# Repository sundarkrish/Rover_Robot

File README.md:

# Rover-Robot
 repository for software, hardware and reference documents related to rover robot project

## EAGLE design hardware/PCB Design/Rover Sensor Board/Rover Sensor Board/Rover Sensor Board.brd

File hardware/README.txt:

schematics, layout, 3D models, gerber files etc.

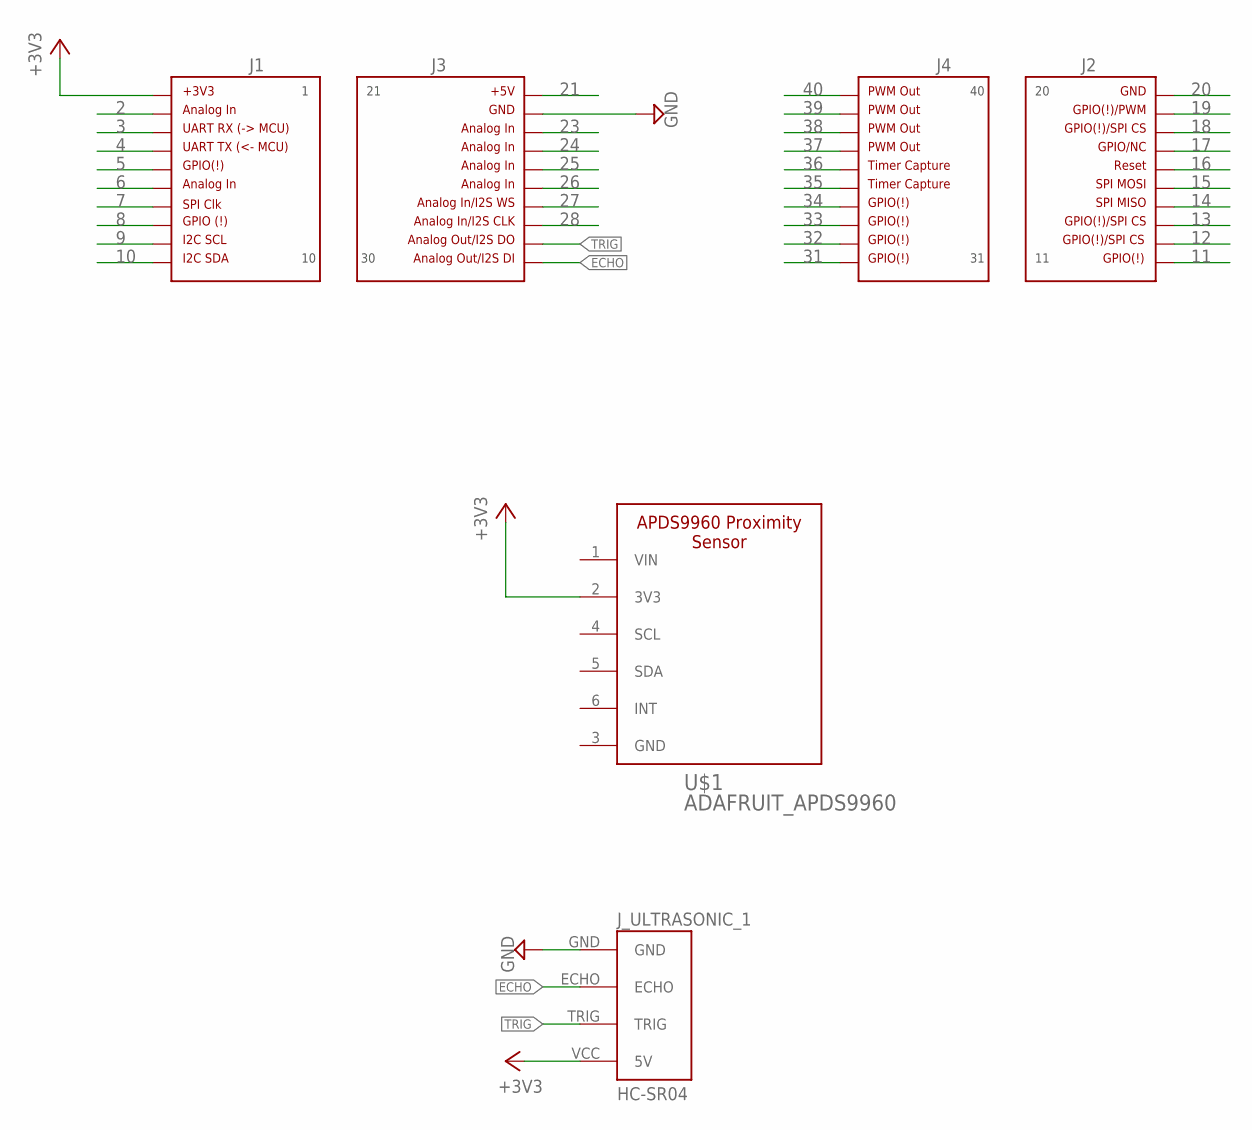
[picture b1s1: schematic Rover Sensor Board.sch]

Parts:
J1: HEADER1X10-J1SILK_LABELS; J1
J2: HEADER1X10-J2SILK_LABELS; J2
J3: HEADER1X10-J3NOSILK; 1X10-J3
J4: HEADER1X10-J4SILK_LABELS; J4
J_ULTRASONIC_1: HC-SR04; HC-SR04_FOOTPRINT
U$1: ADAFRUIT_APDS9960

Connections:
2: J1.2
3: J1.3
4: J1.4
5: J1.5
6: J1.6
7: J1.7
8: J1.8
9: J1.9
10: J1.10
11: J2.11
12: J2.12
13: J2.13
14: J2.14
15: J2.15
16: J2.16
17: J2.17
18: J2.18
19: J2.19
20: J2.20
21: J3.21
23: J3.23
24: J3.24
25: J3.25
26: J3.26
27: J3.27
28: J3.28
31: J4.31
32: J4.32
33: J4.33
34: J4.34
35: J4.35
36: J4.36
37: J4.37
38: J4.38
39: J4.39
40: J4.40
+3V3: J1.1, J_ULTRASONIC_1.VCC (5V), U$1.2 (3V3)
ECHO: J3.30, J_ULTRASONIC_1.ECHO
GND: J3.22, J_ULTRASONIC_1.GND
TRIG: J3.29, J_ULTRASONIC_1.TRIG

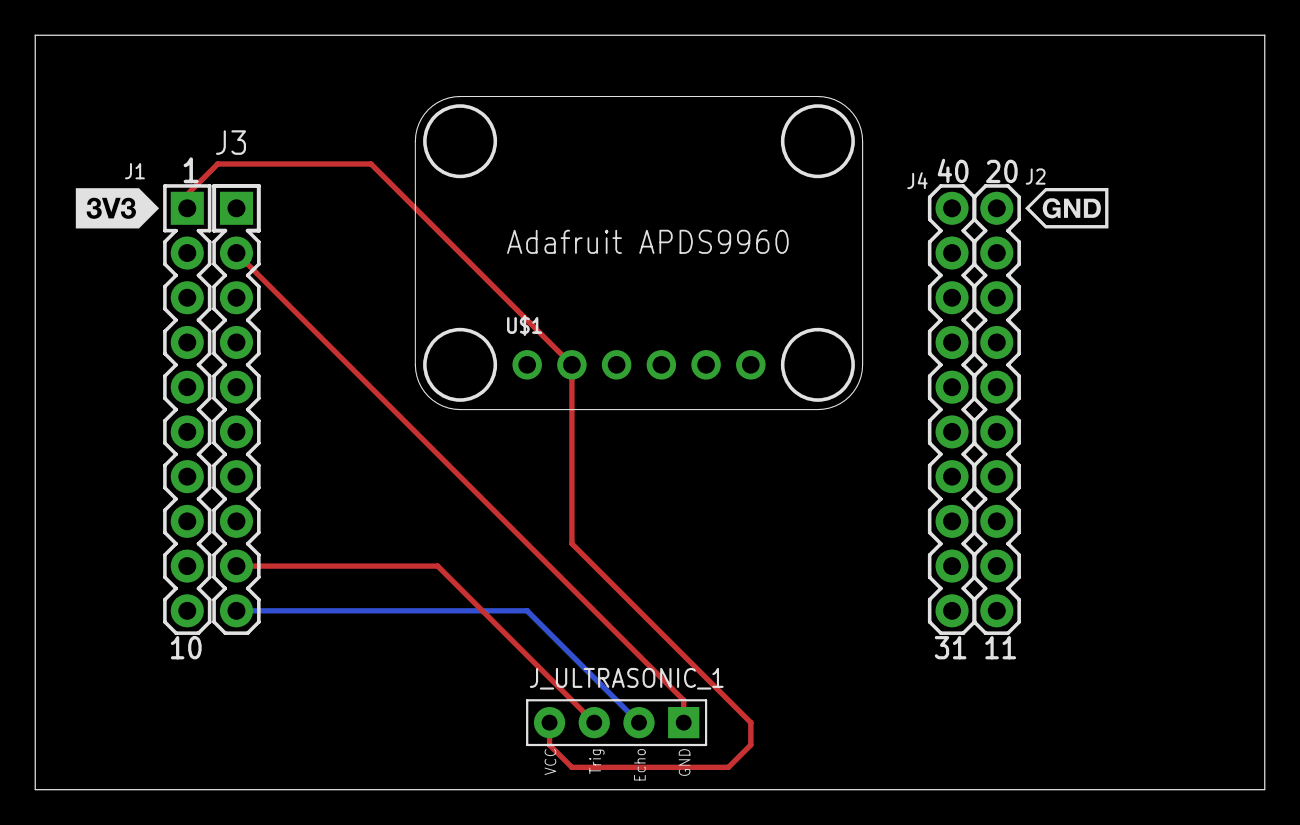
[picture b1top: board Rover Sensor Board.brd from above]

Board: 2 copper layers, 69.8 x 42.9 mm, 6 parts (0 on the bottom side), 4 nets.

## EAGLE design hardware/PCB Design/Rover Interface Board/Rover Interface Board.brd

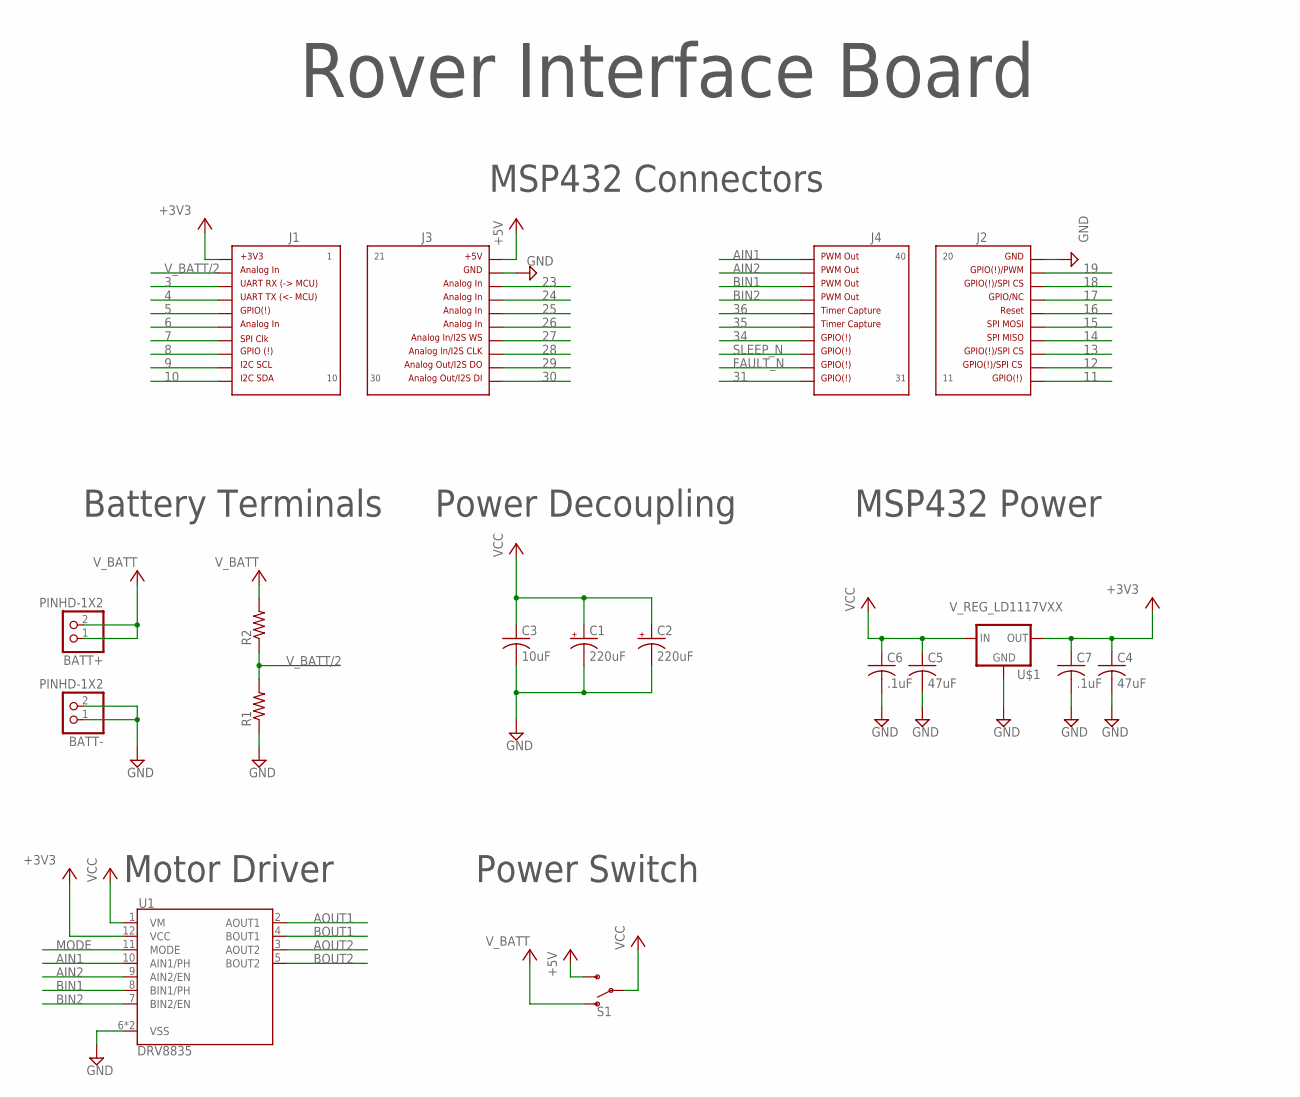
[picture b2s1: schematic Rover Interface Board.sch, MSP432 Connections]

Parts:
BATT+: PINHD-1X2; 1X02
BATT-: PINHD-1X2; 1X02
C1, C2: 220uF; CPOL-RADIAL-5MM-10MM
C3: 10uF; C025-050X050
C4, C5: 47uF; C025-050X050
C6, C7: .1uF; C025-050X050
J1: HEADER1X10-J1SILK_LABELS; J1
J2: HEADER1X10-J2SILK_LABELS; J2
J3: HEADER1X10-J3; J3
J4: HEADER1X10-J4SILK_LABELS; J4
R1, R2: R-US_0204/7; 0204/7
S1: SWITCH-SPDT-PTH-11.6X4.0MM; SWITCH_SPDT_PTH_11.6X4.0MM
U1: DRV8835; WSON-12
U$1: V_REG_LD1117VXX; 78XXL

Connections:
3: J1.3
4: J1.4
5: J1.5
6: J1.6
7: J1.7
8: J1.8
9: J1.9
10: J1.10
11: J2.11
12: J2.12
13: J2.13
14: J2.14
15: J2.15
16: J2.16
17: J2.17
18: J2.18
19: J2.19
23: J3.23
24: J3.24
25: J3.25
26: J3.26
27: J3.27
28: J3.28
29: J3.29
30: J3.30
31: J4.31
34: J4.34
35: J4.35
36: J4.36
+3V3: C4.1, C7.1, J1.1, U1.12 (VCC), U$1.GND (OUT)
+5V: J3.21, S1.3 (S)
AIN1: J4.40, U1.10 (AIN1/PH)
AIN2: J4.39, U1.9 (AIN2/EN)
AOUT1: U1.2 (AOUT1)
AOUT2: U1.3 (AOUT2)
BIN1: J4.38, U1.8 (BIN1/PH)
BIN2: J4.37, U1.7 (BIN2/EN)
BOUT1: U1.4 (BOUT1)
BOUT2: U1.5 (BOUT2)
FAULT_N: J4.32
GND: BATT-.1, BATT-.2, C1.-, C2.-, C3.2, C4.2, C5.2, C6.2, C7.2, J2.20, J3.22, R1.1, U1.6 (VSS), U1.PAD (VSS), U$1.IN (GND)
MODE: U1.11 (MODE)
SLEEP_N: J4.33
VCC: C1.+, C2.+, C3.1, C5.1, C6.1, S1.2, U1.1 (VM), U$1.OUT (IN)
V_BATT: BATT+.1, BATT+.2, R2.2, S1.1 (O)
V_BATT/2: J1.2, R1.2, R2.1

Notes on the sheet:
Rover Interface Board
Battery Terminals
Power Decoupling
MSP432 Power
MSP432 Connectors
Power Switch
Motor Driver

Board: 2 copper layers, 18 parts (0 on the bottom side), 10 nets, no tracks yet.

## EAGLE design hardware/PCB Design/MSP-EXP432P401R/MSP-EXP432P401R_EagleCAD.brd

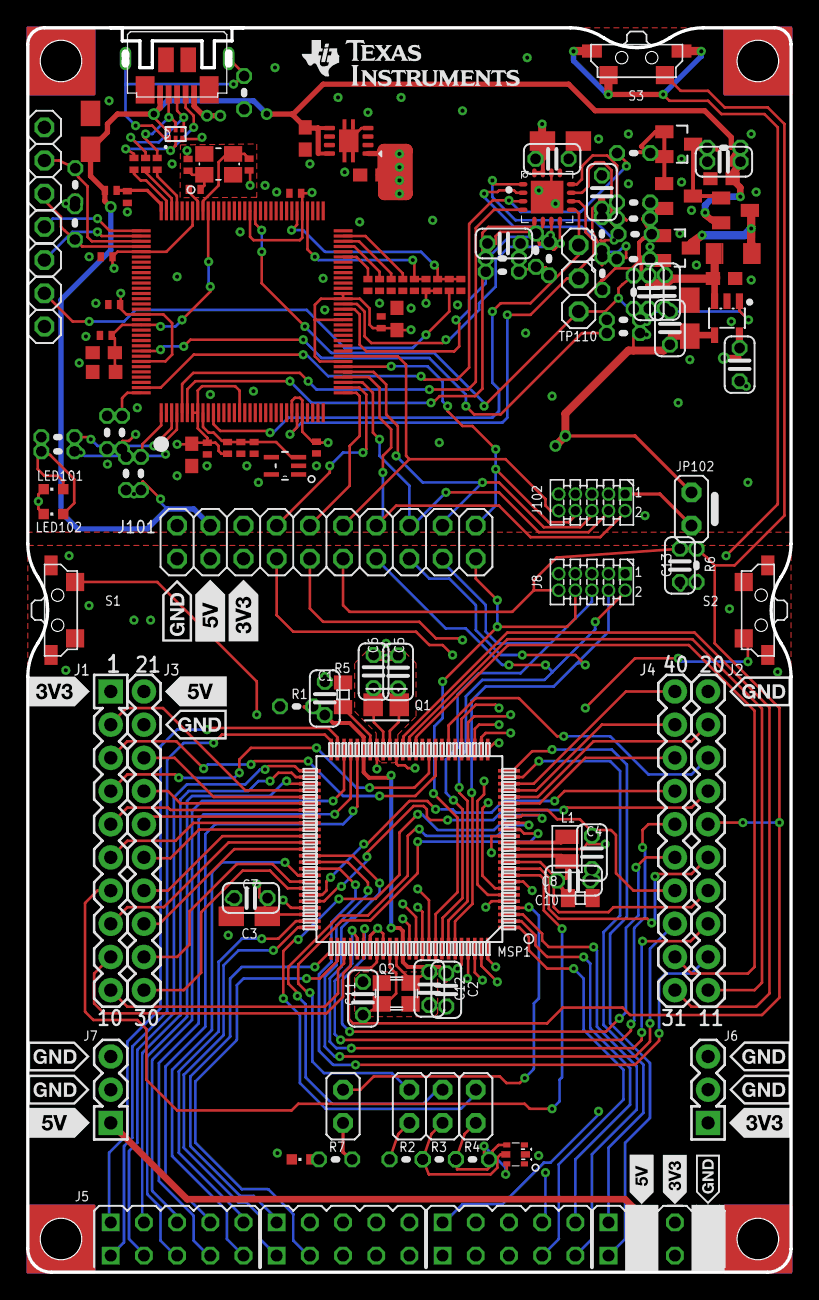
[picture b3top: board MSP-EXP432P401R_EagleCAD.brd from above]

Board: 4 copper layers, 58.1 x 94.9 mm, 150 parts (0 on the bottom side), 160 nets.

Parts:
C1, C2, C4, C7, C8, C118, C120, C124, C129: 100n; C025-024X044
C3: 10u; A/3216-18R
C5, C6, C11, C12: 22p; C025-024X044
C10: 4u7; CSMD0805
C13: 1n; C025-024X044
C101, C102: 12pF; C0402
C103, C131, C150: 0.1uF; C0402
C104, C110, C112, C114, C123: 10n; C0402
C105: 2u2; C0603
C106, C140: 4.7u; A/3216-18R
C107, C130, C132, C141: 1u; C0603
C108: DNP; C0402
C111, C113, C121: 100n; C0402
C115, C116: 33p; C025-024X044
C117, C119: 4.7u; C0603
C126, C127: 220n; C025-024X044
C128: 47u; A/3216-18R
C133: 2.2uF; C0603K
D101, D102: BAS40-05; SOT23
IC101: TPS73533DRB; SON8
IC102: TPD4E004_DRY_6; DRY6
IC103: TPS2102DBV; SOT23-5
IC106: TM4C129ENCPDT; TQFP-128
IC107: LM4040B25_DCK_5; DCK5
J1: J1
J2: J2
J3: J3
J4: J4
J5: EDGE_CON; BOTTOM_CONNECTOR
J6: HEADER 1X03; 3PIN_PWR_3V3
J7: BP_HEADERS_PWR_5V; 3PIN_PWR_5V
J8, J102: ARM-10
J101: J101_432
JP8: LED1; JP1M
JP9: LED2_RED; JP1M
JP10: LED2_GREEN; JP1M
JP11: LED2_BLUE; JP1M
JP102: JP1M
L1: 4.7uH; 0806
L101: 2u2; L3216C
LED1, LED101, LED102: CHIPLED_0603
LED2: EVERLIGHT_19-337; RGB_LED
MSP1: MSP432; PZ100
MSP101: MSP430G2452IRSA16R; RSA16
Q1: LF_XTAL
Q2: FA-238
Q101: NX3225GA_OSC; NX3225GA
R1: 0R; 0204V
R2: 110R; 0204V
R3: 16R; 0204V
R4: 24R; 0204V
R5: 91kOhm, 0.1%, 25ppm/C; 0805
R6, R107: 47k; 0204V
R7, R111, R120, R124: 470; 0204V
R101, R134: DNP; 0204V
R102: 100; R0402
R103: 10k; R0402
R104, R140: 51; R0402
R105: 1k 1%; R0402
R106: 2R; R0402
R108, R109, R110: 1k; R0402
R112, R113, R114, R115, R133, R135, R136: 220k; 0204V
R116, R117: 4k7; 0204V
R118: 820; 0204V
R119: 0; 0204V
R123: 33; 0204V
R125, R129: 10k; 0204V
R126: 2k2; 0204V
R127: 3k3; 0204V
R128: 6k8; 0204V
R131, R137, R138: 0; R0402
R132: 330k; 0204V
R139: dnp; R0402
S1, S2, S3: TS-1188E
T101: DMG1013UW; SOT23
T102: BC850CW-115; SOT23-BEC
TP101, TP102, TP103, TP104, TP105, TP106, TP107, TP108, TP109, TP110: TEST_PIN2; 1X01
U$1, U$2, U$3, U$5: MOUNTHOLE_125MIL
U$4: LOGO16_TPLACE
U$7: MIKE_TM
U$8: P401R_REARSILK_REV2_1
U$9: REAR_TILOGO
U$10: COMPLIANCE_SUITESYMBOLONLY; EVM_COMPLIANCESUITE_SYMBOLONLY
U$11: COMPLIANCE_FCC_TEXTREAR; COMPLIANCE_FCC_TEXT
U$12: LOGO-ROCKET
U$13: P401R_SILKLABEL; SILKLABELUPDATED
USB101: MOLEX_105164-0001

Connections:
!RST: C13.1, J2.16, J8.10, J101.11, MSP1.83, R6.1, S3.S1
+3V3: C3.+, C4.1, C7.1, J1.1, J5.35, J5.36, J6.1, J8.1, J101.5, MSP1.13, MSP1.73, R1.1, R6.2
+5V: J3.21, J5.33, J5.34, J7.1, J101.3
AVCC: C116.2, MSP101.6, R114.2, R115.1
AVCCOUT: C115.2, MSP101.1, R112.2, R113.1
DCDCCAL0: MSP101.12, R126.2
DCDCCAL1: MSP101.2, R127.2
DCDCCAL2: MSP101.11, R128.2
DCDCIO0: IC106.P$5, MSP101.4
DCDCIO1: IC106.P$6, MSP101.5
DCDCPULSE: IC106.P$127, MSP101.3, R118.2
DCDCRST: IC106.P$11, MSP101.9, TP108.1
DCDCTEST: IC106.P$27, MSP101.10, TP109.1
DCOR: MSP1.44, R5.1
HOSTSCL: IC106.P$49, MSP101.7, R117.2
HOSTSDA: IC106.P$50, MSP101.8, R116.2
IRSTN: R102.1, TP106.1
ITCK: IC106.P$100, R129.1, TP103.1
ITDI: IC106.P$98, TP105.1
ITDO: IC106.P$97, TP104.1
ITMS: IC106.P$99, R125.1, TP102.1
LED0: IC106.P$3, R111.1
LED1: IC106.P$4, R124.1
unnamed: J102.1, JP102.2
unnamed: IC106.P$63, R108.2
unnamed: LED102.A, R124.2
unnamed: C1.1, C2.1, MSP1.45, MSP1.87, R1.2
unnamed: LED101.A, R111.2
unnamed: JP9.2, R2.1
unnamed: LED2.5, R2.2
unnamed: LED2.6, R3.2
unnamed: LED2.4, R4.2
unnamed: R119.1, T102.E
unnamed: D101.1, D101.2, R118.1, T102.B
unnamed: D102.3, L101.1, T101.3
unnamed: D101.3, R120.2, T101.1, T102.C
unnamed: LED1.A, R7.2
unnamed: JP10.2, R3.1
unnamed: IC106.P$93, R138.2
unnamed: IC106.P$61, R110.2
unnamed: IC106.P$95, R131.2
unnamed: JP11.2, R4.1
unnamed: IC106.P$62, R109.2
unnamed: JP8.2, R7.1
unnamed: C6.1, MSP1.42, Q1.1
unnamed: C5.1, MSP1.41, Q1.2
unnamed: IC106.P$59, R139.2
OSC0: C102.1, IC106.P$88, Q101.3
OSC1: IC106.P$89, R106.2
OSC1_R: C101.1, Q101.1, R106.1
P1.0_LED1: JP8.1, MSP1.4
P1.1_BUTTON1: MSP1.5, S1.S1
P1.2_BCLUART_RXD: J101.7, MSP1.6
P1.3_BCLUART_TXD: J101.9, MSP1.7
P1.4_BUTTON2: MSP1.8, S2.S1
P1.5_SPICLK_J1.7: J1.7, MSP1.9
P1.6_SPIMOSI_J2.15: J2.15, MSP1.10
P1.7_SPIMISO_J2.14: J2.14, MSP1.11
P2.0_RGBLED_RED: JP9.1, MSP1.16
P2.1_RGBLED_GREEN: JP10.1, MSP1.17
P2.2_RGBLED_BLUE: JP11.1, MSP1.18
P2.3_IO_J4.34: J4.34, MSP1.19
P2.4_PWM_J4.38: J4.38, MSP1.20
P2.5_PWM_J2.19: J2.19, MSP1.21
P2.6_PWM_J4.39: J4.39, MSP1.22
P2.7_PWM_J4.40: J4.40, MSP1.23
P3.0_IO_J2.18: J2.18, MSP1.32
P3.2_URXD_J1.3: J1.3, MSP1.34
P3.3_UTXD_J1.4: J1.4, MSP1.35
P3.5_IO_J4.32: J4.32, MSP1.37
P3.6_IO_J2.11: J2.11, MSP1.38
P3.7_IO_J4.31: J4.31, MSP1.39
P4.0_A13_J3.24: J3.24, MSP1.56
P4.1_IO_J1.5: J1.5, MSP1.57
P4.2_A11_J3.25: J3.25, MSP1.58
P4.3_A10_J1.6: J1.6, MSP1.59
P4.4_A9_J3.26: J3.26, MSP1.60
P4.5_A8_J3.27: J3.27, MSP1.61
P4.6_IO_J1.8: J1.8, MSP1.62
P4.7_A6_J3.28: J3.28, MSP1.63
P5.0_IO_J2.13: J2.13, MSP1.64
P5.1_IO_J4.33: J4.33, MSP1.65
P5.2/XT2IN: C12.1, MSP1.86, Q2.1
P5.2_IO_J2.12: J2.12, MSP1.66
P5.3: J5.9, MSP1.67
P5.3/XT2OUT: C11.1, MSP1.85, Q2.3
P5.4_IO_J3.29: J3.29, MSP1.68
P5.5_IO_J3.30: J3.30, MSP1.69
P5.6_PWM_J4.37: J4.37, MSP1.70
P5.7_IO_J2.17: J2.17, MSP1.71
P6.0_A15_J1.2: J1.2, MSP1.54
P6.1_A14_J3.23: J3.23, MSP1.55
P6.2: J5.12, MSP1.76
P6.3: J5.13, MSP1.77
P6.4_I2CSDA_J1.10: J1.10, MSP1.78
P6.5_I2CSCL_J1.9: J1.9, MSP1.79
P6.6_CAPTURE_J4.36: J4.36, MSP1.80
P6.7_CAPTURE_J4.35: J4.35, MSP1.81
P7.0: J5.17, MSP1.88
P7.1: J5.16, MSP1.89
P7.2: J5.15, MSP1.90
P7.3: J5.14, MSP1.91
P7.4: J5.24, MSP1.26
P7.5: J5.23, MSP1.27
P7.6: J5.26, MSP1.28
P7.7: J5.25, MSP1.29
P8.0: J5.22, MSP1.30
P8.2: J5.8, MSP1.46
P8.3: J5.7, MSP1.47
P8.4: J5.6, MSP1.48
P8.5: J5.2, MSP1.49
P8.6: J5.1, MSP1.50
P8.7: J5.3, MSP1.51
P9.0: J5.4, MSP1.52
P9.1: J5.5, MSP1.53
P9.2: J5.10, MSP1.74
P9.3: J5.11, MSP1.75
P9.4: J5.18, MSP1.96
P9.5: J5.19, MSP1.97
P9.6: J5.20, MSP1.98
P9.7: J5.21, MSP1.99
P10.0: J5.28, MSP1.100
P10.1: J5.27, MSP1.1
P10.2: J5.30, MSP1.2
P10.3: J5.29, MSP1.3
P10.4: J5.32, MSP1.24
P10.5: J5.31, MSP1.25
P96VBUS: C150.1, IC106.P$96, R140.2
REF_MAIN_LDO: IC106.P$128, R135.2, R136.2
REF_TARGET_VCC: IC106.P$120, R101.2, R134.2
TCK_SWDCLK: J8.4, J101.15, MSP1.95
TDI: J8.8, J101.19, MSP1.92
TDO_SWO: J8.6, J101.17, MSP1.93
TMS_SWDIO: J8.2, J101.13, MSP1.94
VBUS_DETECT: IC106.P$1, R132.2, R133.2
VCCEN1: IC103.1, IC106.P$78, R107.1, TP110.1
VCORE: C8.1, C10.1, L1.1, MSP1.12
VDDC: C131.1, C132.2, C133.1, IC106.P$87, IC106.P$115
VREFA+: C110.1, C111.1, IC106.P$9, IC107.3, R105.1
VSW: L1.2, MSP1.14
XDS-GND: C1.2, C2.2, C3.-, C4.2, C5.2, C6.2, C7.2, C8.2, C10.2, C11.2, C12.2, C13.2, J2.20, J3.22, J5.37, J5.38, J6.2, J6.3, J7.2, J7.3, J8.3, J8.5, J8.7, J8.9, J101.1, LED1.C, LED2.1, LED2.2, LED2.3, MSP1.15, MSP1.40, MSP1.43, MSP1.72, MSP1.82, MSP1.84, R5.2, S1.G1, S1.G2, S1.S2, S2.G1, S2.G2, S2.S2, S3.G1, S3.G2, S3.S2
XDSET_!RST: C108.1, IC106.P$70, R102.2, R103.2
XDSET_DM: IC102.5, R138.1, USB101.D-
XDSET_DP: IC102.4, R137.1, USB101.D+
XDSET_DPR: IC106.P$94, R137.2
XDSET_GND: C101.2, C102.2, C103.2, C104.2, C105.2, C106.-, C107.2, C108.2, C110.2, C111.2, C112.2, C113.2, C114.2, C115.1, C116.1, C117.2, C118.2, C119.2, C120.2, C121.2, C123.2, C124.2, C126.2, C127.2, C128.-, C129.2, C130.1, C131.2, C132.1, C133.2, C140.-, C141.2, C150.2, D102.1, D102.2, IC101.4, IC101.9, IC102.3, IC103.2, IC106.P$10, IC106.P$17, IC106.P$48, IC106.P$55, IC106.P$58, IC106.P$64, IC106.P$66, IC106.P$80, IC106.P$114, IC107.1, J101.2, J102.3, J102.5, J102.7, J102.9, LED101.C, LED102.C, MSP101.13, MSP101.14, MSP101.TP, R101.1, R107.2, R108.1, R109.1, R110.1, R113.2, R115.2, R119.2, R123.2, R133.1, R136.1, R139.1, TP101.1, USB101.GND
XDSET_ID: IC102.2, R131.1, USB101.ID
XDSET_RESET_OUT: IC106.P$40, J101.12, J102.10
XDSET_RXD: IC106.P$33, J101.10
XDSET_SHIELD: IC102.1, R123.1, USB101.SHIELD_TH1, USB101.SHIELD_TH2
XDSET_TCK_SWDCLK: IC106.P$35, J101.16, J102.4
XDSET_TDI: IC106.P$38, J101.20, J102.8
XDSET_TDO_SWO: IC106.P$37, J101.18, J102.6
XDSET_TMS_SWDIO: IC106.P$36, J101.14, J102.2
XDSET_TXD: IC106.P$34, J101.8
XDSET_VBAT: C103.1, IC106.P$68, R104.2
XDSET_VBUS: C117.1, C118.1, C140.+, C141.1, IC101.5, IC101.8, IC102.6, J101.4, R120.1, R132.1, R140.1, T101.2, USB101.VBUS
XDSET_VCC: C104.1, C105.1, C106.+, C107.1, C112.1, C113.1, C114.1, C121.1, C123.1, C124.1, C126.1, C130.2, IC101.1, IC103.5, IC106.P$7, IC106.P$8, IC106.P$16, IC106.P$26, IC106.P$28, IC106.P$39, IC106.P$47, IC106.P$51, IC106.P$52, IC106.P$69, IC106.P$79, IC106.P$90, IC106.P$101, IC106.P$113, IC106.P$122, MSP101.15, MSP101.16, R103.1, R104.1, R105.2, R114.1, R116.1, R117.1, R125.2, R129.2, R135.1, TP107.1
XDSET_VCCOUT: C119.1, C120.1, C127.1, IC103.3, L101.2, R112.1, R126.1, R127.1, R128.1
XDSET_VCCTARGET: C128.+, C129.1, IC103.4, J101.6, JP102.1, R134.1

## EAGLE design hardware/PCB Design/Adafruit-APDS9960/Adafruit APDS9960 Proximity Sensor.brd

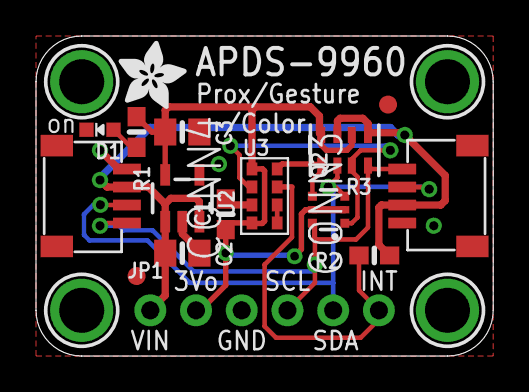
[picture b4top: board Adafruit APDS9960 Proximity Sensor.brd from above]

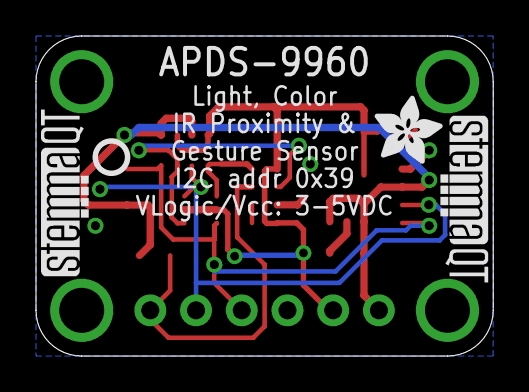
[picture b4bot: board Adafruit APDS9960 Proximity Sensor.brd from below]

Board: 2 copper layers, 25.4 x 17.8 mm, 24 parts (4 on the bottom side), 10 nets.

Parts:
C1: 0.1uF; 0603-NO
C2, C3: 10uF; 0805-NO
CONN3, CONN4: STEMMA_I2C_QT; JST_SH4
D1: GREEN; CHIPLED_0603_NOOUTLINE
FID3, FID4: FIDUCIAL_1MM
JP1: 1X06_ROUND_70
Q2: BSS138; SOT363
R1, R2: 10K; 0603-NO
R3: 10K; RESPACK_4X0603
U2: AP2112K-3.3; SOT23-5
U3: APDS-9960
U$1, U$17, U$19, U$21: MOUNTINGHOLE2.5; MOUNTINGHOLE_2.5_PLATED
U$2, U$22: ADAFRUIT_3.5MM
U$25: PCBFEAT-REV-040
U$30, U$31: STEMMAQT

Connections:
3.3V: C1.1, C3.1, JP1.2, Q2.2, Q2.5, R1.1, R3.2, R3.4, U2.5, U3.5, U3.8
GND: C1.2, C2.2, C3.2, CONN3.1, CONN4.1, D1.C, JP1.3, U2.2, U3.6
INT: JP1.6, R2.2, U3.2
unnamed: D1.A, R1.2
unnamed: U3.3, U3.4
SCL: CONN3.4, CONN4.4, JP1.4, Q2.6, R3.8
SCL_3V: Q2.1, R3.7, U3.7
SDA: CONN3.3, CONN4.3, JP1.5, Q2.3, R3.6
SDA_3V: Q2.4, R3.5, U3.1
VCC: C2.1, CONN3.2, CONN4.2, JP1.1, R2.1, R3.1, R3.3, U2.1, U2.3

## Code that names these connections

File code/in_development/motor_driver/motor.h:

/*--------------------------------------------------------------------------------------------
*motor.h
*Parker McDonnell
*ECEN 5613 -- Spring 2020 - Prof. McClure
*University of Colorado Boulder
*
*---------------------------------------------------------------------------------------------
*Code Reuse:
*
**------------------------------------------------------------------------------------------*/

#ifndef _MOTOR_H_
#define _MOTOR_H_

//-------------------------------------------------------------------------------------------
//                                       INCLUDES
//-------------------------------------------------------------------------------------------

//libraries
#include "msp.h"
#include <stdio.h>
#include <stdlib.h>
#include <stdint.h>
#include <stdbool.h>

//-------------------------------------------------------------------------------------------
//                                        DEFINES
//-------------------------------------------------------------------------------------------

#define AIN1            0x0080              //P2.7
#define AIN2            0x0040              //P2.6
#define BIN1            0x0010              //P2.4
#define BIN2            0x0040              //P5.6
#define SLEEP_N         0x0002              //P5.1
#define FAULT_N         0x0020              //P3.5

#define _MOTOR_DEBUG_

//-------------------------------------------------------------------------------------------
//                                  EXTERNAL VARIABLES
//-------------------------------------------------------------------------------------------

typedef enum{
    forward,
    reverse,
    left,
    right,
    stopped
}direction_t;

typedef struct{
    uint8_t speed;
    uint8_t time;
    //drv8833_t driver;
    direction_t direction;
    bool running;
    bool sleep;
    bool fault;
}status_t;

//-------------------------------------------------------------------------------------------
//                              PUBLIC FUNCTION PROTOTYPES
//-------------------------------------------------------------------------------------------

/////////////////////////////////////////////////////////////////////////////////////////////
//void function(void)
/////////////////////////////////////////////////////////////////////////////////////////////
//@brief:
//
//
//@param:
//@return:
//@outcome:
/////////////////////////////////////////////////////////////////////////////////////////////

void motor_init(void);

/////////////////////////////////////////////////////////////////////////////////////////////
//void function(void)
/////////////////////////////////////////////////////////////////////////////////////////////
//@brief:
//
//
//@param:
//@return:
//@outcome:
/////////////////////////////////////////////////////////////////////////////////////////////

bool motor_fault(void);

/////////////////////////////////////////////////////////////////////////////////////////////
//void function(void)
/////////////////////////////////////////////////////////////////////////////////////////////
//@brief:
//
//
//@param:
//@return:
//@outcome:
/////////////////////////////////////////////////////////////////////////////////////////////

void motor_stop(void);

/////////////////////////////////////////////////////////////////////////////////////////////
//void function(void)
/////////////////////////////////////////////////////////////////////////////////////////////
//@brief:
//
//
//@param:
//@return:
//@outcome:
/////////////////////////////////////////////////////////////////////////////////////////////

bool motor_go(uint8_t direction, uint8_t speed, uint8_t time_sec);

#endif  //_MOTOR_H_

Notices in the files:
hardware/PCB Design/MSP-EXP432P401R/MSP-EXP432P401R_EagleCAD.brd:
(C)2003 A. DANNENBERG
parts and their libraries:
microbuilder: This work is placed in the public domain, and may be freely used for commercial and non-commercial work with the following conditions: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
SparkFun-IC-Power: Licensing: Creative Commons ShareAlike 4.0 International - https://creativecommons.org/licenses/by-sa/4.0
